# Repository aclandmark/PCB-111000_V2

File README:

PCB111000 has beeen developed as a learning aid for the C language when applied to AVR devices.  
It consists of a USB bridge to communicate with a PC, an 8 digit display and two AVR devices. 
One of the AVR devices (Atmega 328) hosts a programmer and miniOS which drives the display, 
the other (Atmega168), the user device, hosts user projects.

An I2C bus is used to link the two devices.
All user projects are compiled using Arduino, system projects use Arduino or Studio 7 if needed.
The boards are set up using the UNO to host a bespoke programer.  See repository "UNO_as_an_AVR_programer". 

See repository "PCB-111000/1_Documentation/1_PCB 111000 leaflet.pdf" for general information and a block diagram of the original development. 

There are three versions of PCB111000:

PCB_111000_V2 using two Atmega devices and the FTDI FT230XS USB bridge
PCB_111000_UNO_V2 A simplified plug in version for use with the UNO
PCB_111000_CP2102 Using one Atmega one ATtiny and a CP2102 module for USB connectivity.

In PCB_111000_UNO_V2 and PCB_111000_CP2102 the user device is an Atmega328 which hosts
a bootloader as well as the user projects.

In PCB_111000_CP2102 the I2C bus is replaced with a one wire firmware UART.

Originally 56 projects were developed for use with PCB111000.
These have been revised over the years and are now as follows

20 very short projects provided to show what a C program looks like and explore basic methods of program flow control
9 projects exploring the operation of the recever transmitter (USART) block
7 projects exploring interrupts
4 projects exploring bit operatons, division and the conversion between 8 bit binary and decimal numbers
11 projects based on the Arduino USART library with reset analysis including
	Interger, prime and scientific numbers
	Integer roots and a pie estimator
	Power series to compute real number powers and trig functions
	A floating point number to string sbroutine
	Displays to simulate gravity, the pendulum and a noise waveform.
9 Projects to Illustate driving the display from the keyboard and user switches, includes a simple
calculator and floating point number to 8 digit display.
7 Projects used to build simple clocks and stop watches
6 Projects used to illustrate use of Atmel Studio 7
8 projects used to illustrate the operation of floating point numbers, tested using power series as above
and the generation of pulse and sawtooth waveforms by supperimposing sine wave upon one another.
5 projects to test the operation of the PCB during assembly
5 projects used to exlore the calibration of the RC oscillators used to clock the devices.

Any bugs:	Of course there are especially in the conversion of a floating point number to 8 digits.
		Initially I tried to fix them, but stopped.  If they are of no interest to ayone else 
		then they are of no nterest to me either.

Projects for  PCB_111000_UNO_V2 and PCB_111000_CP2102:  Projects and the mini-OS for each of these pcbs 
requires updating however both include most of the initial projects.

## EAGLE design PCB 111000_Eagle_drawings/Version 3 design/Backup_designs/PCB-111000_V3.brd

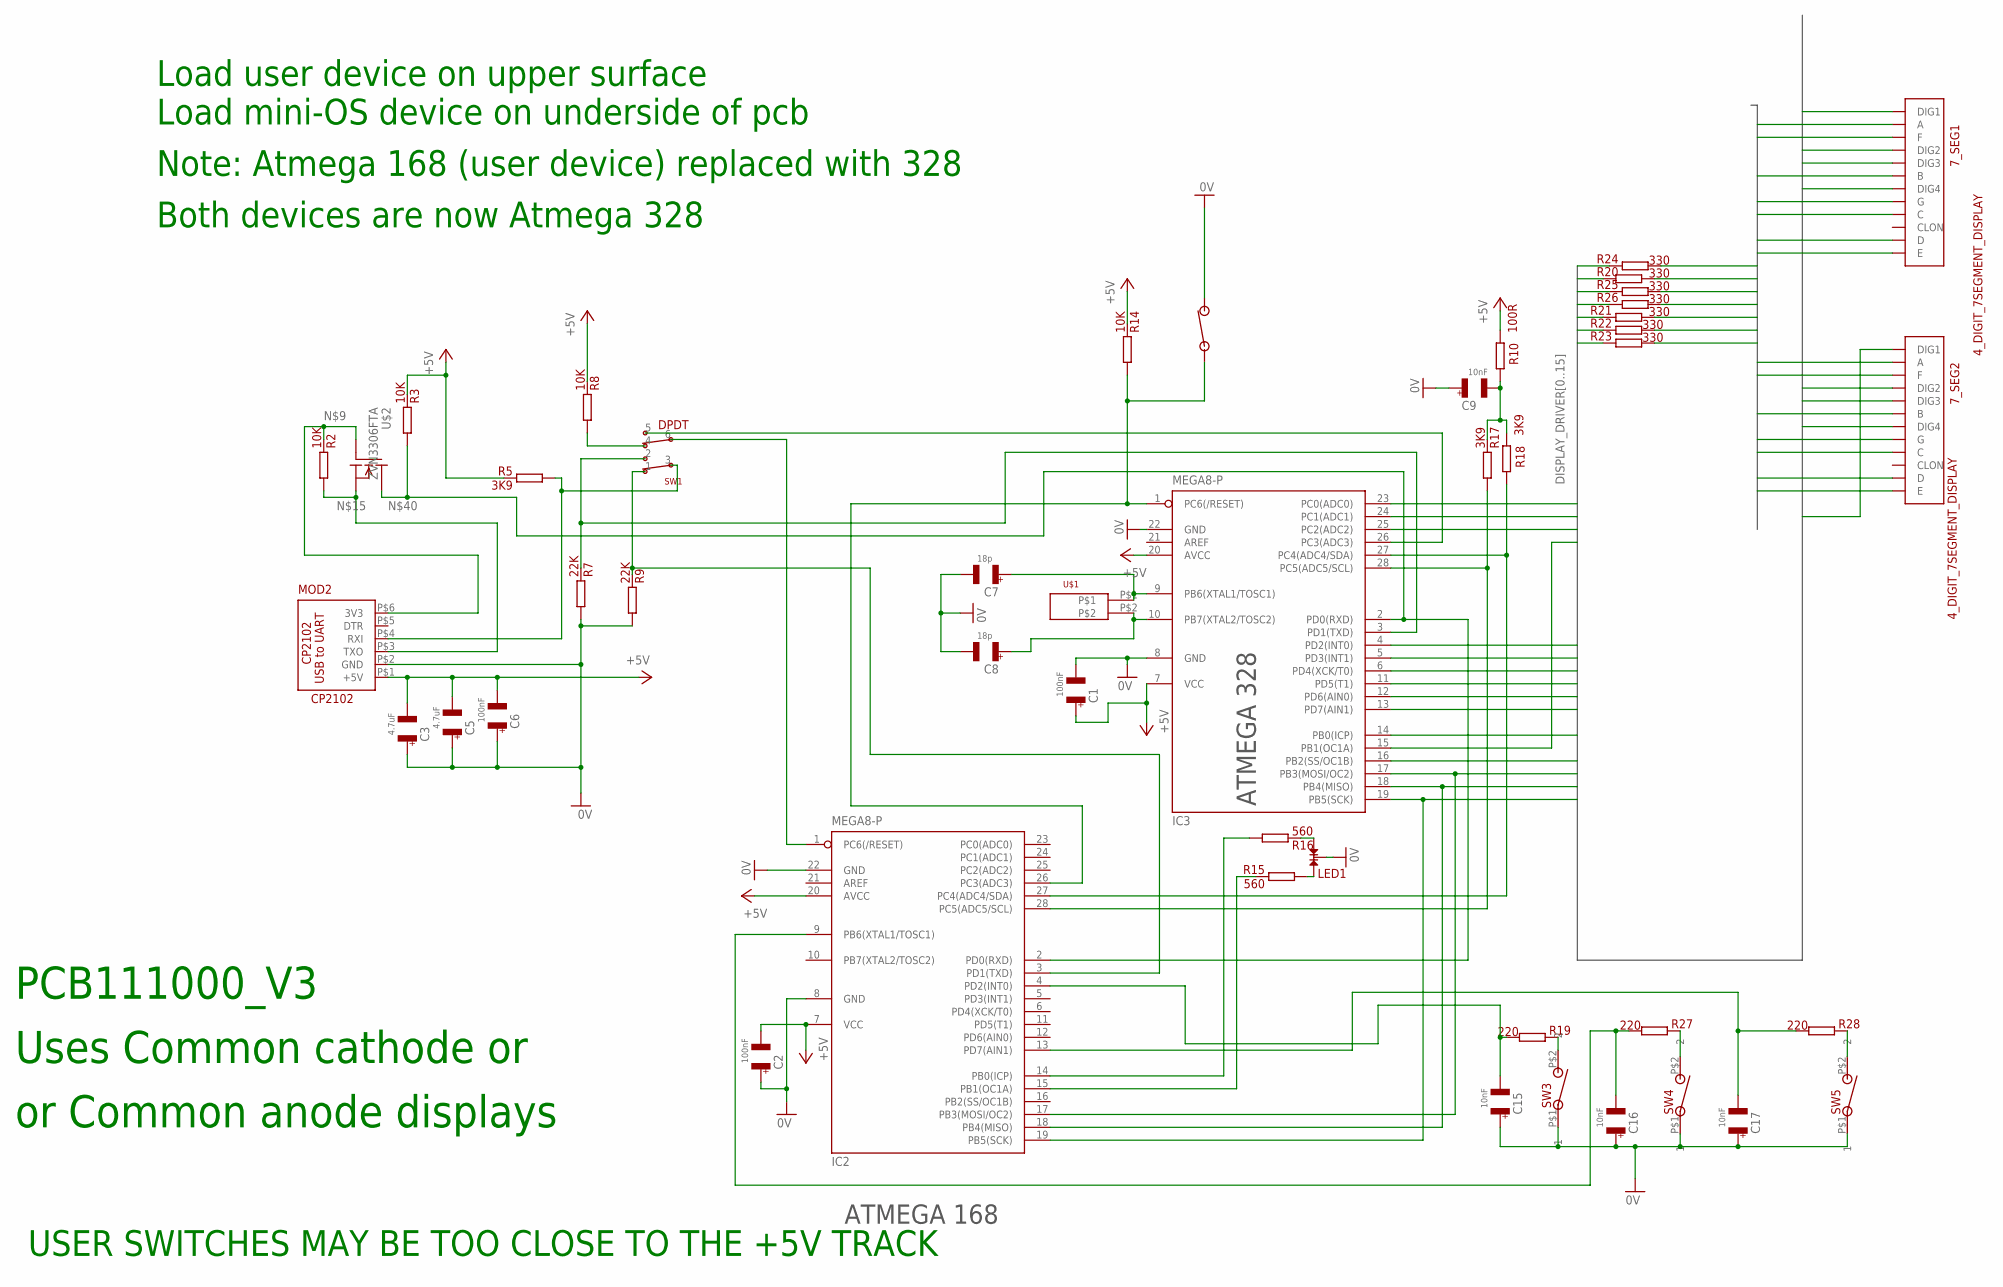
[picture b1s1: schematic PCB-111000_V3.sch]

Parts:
7_SEG1, 7_SEG2: 4_DIGIT_7SEGMENT_DISPLAY
C1, C2, C6: 100nF; 1206@1
C3, C5: 4.7uF; 1206@1
C7, C8: 18p; 0805
C9, C15, C16, C17: 10nF; 1206@1
IC2, IC3: MEGA8-P; DIL28-3
LED1: LED; CA_DUAL_LED
MOD2: CP2102
R2, R3, R8, R14: 10K; 1206
R5, R17, R18: 3K9; 1206
R7, R9: 22K; 1206
R10: 100R; 1206
R15, R16: 560; 1206
R19, R27, R28: 220; 1206
R20, R21, R22, R23, R24, R25, R26: 330; 1206
SW1: DPDT; DPDT_SWITCH
SW2: NO_SW; SM_NO_PUSH_BUTTON
SW3, SW4, SW5: NO_PB_1; RE51-0711
U$1: XTAL; XTAL_VIAS
U$2: ZVN3306FTA; SOT-23

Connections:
0V: C1.P$2 (2), C2.P$1 (1), C3.P$1 (1), C5.P$1 (1), C6.P$1 (1), C7.2, C8.2, C9.P$1 (1), C15.P$1 (1), C16.P$1 (1), C17.P$1 (1), IC2.8 (GND), IC2.22 (GND), IC3.8 (GND), IC3.22 (GND), LED1.2, MOD2.P$2 (GND), R7.P$1, R9.P$1, SW2.P$2 (2), SW3.P$1 (1), SW4.P$1 (1), SW5.P$1 (1)
+5V: C1.P$1 (1), C2.P$2 (2), C3.P$2 (2), C5.P$2 (2), C6.P$2 (2), IC2.7 (VCC), IC2.20 (AVCC), IC3.7 (VCC), IC3.20 (AVCC), MOD2.P$1 (+5V), R3.P$2, R5.P$2, R8.P$2, R10.P$2, R14.P$2
DISPLAY_DRIVER0: IC3.15 (PB1(OC1A)), R24.P$2
DISPLAY_DRIVER1: IC3.4 (PD2(INT0)), R20.P$2
DISPLAY_DRIVER2: IC3.5 (PD3(INT1)), R25.P$2
DISPLAY_DRIVER3: IC3.6 (PD4(XCK/T0)), R26.P$2
DISPLAY_DRIVER4: IC3.11 (PD5(T1)), R21.P$2
DISPLAY_DRIVER5: IC3.12 (PD6(AIN0)), R22.P$2
DISPLAY_DRIVER6: IC3.13 (PD7(AIN1)), R23.P$2
DISPLAY_DRIVER8: 7_SEG2.P$12 (DIG1), IC3.14 (PB0(ICP))
DISPLAY_DRIVER9: 7_SEG2.P$9 (DIG2), IC3.16 (PB2(SS/OC1B))
DISPLAY_DRIVER10: 7_SEG2.P$8 (DIG3), IC2.17 (PB3(MOSI/OC2)), IC3.17 (PB3(MOSI/OC2))
DISPLAY_DRIVER11: 7_SEG2.P$6 (DIG4), IC2.18 (PB4(MISO)), IC3.18 (PB4(MISO))
DISPLAY_DRIVER12: 7_SEG1.P$12 (DIG1), IC2.19 (PB5(SCK)), IC3.19 (PB5(SCK))
DISPLAY_DRIVER13: 7_SEG1.P$9 (DIG2), IC3.23 (PC0(ADC0))
DISPLAY_DRIVER14: 7_SEG1.P$8 (DIG3), IC3.24 (PC1(ADC1))
DISPLAY_DRIVER15: 7_SEG1.P$6 (DIG4), IC3.25 (PC2(ADC2))
unnamed: IC2.14 (PB0(ICP)), R16.P$1
unnamed: IC2.15 (PB1(OC1A)), R15.P$2
unnamed: LED1.1, R15.P$1
unnamed: LED1.3, R16.P$2
unnamed: IC3.26 (PC3(ADC3)), SW1.5
unnamed: IC3.3 (PD1(TXD)), R7.P$2, SW1.2
unnamed: R27.P$2, SW4.P$2 (2)
unnamed: R19.P$2, SW3.P$2 (2)
unnamed: MOD2.P$6 (3V3), R2.P$2, U$2.3 (G)
unnamed: C7.1, IC3.9 (PB6(XTAL1/TOSC1)), U$1.P$1
unnamed: C17.P$2 (2), IC2.13 (PD7(AIN1)), R28.P$1
unnamed: C8.1, IC3.10 (PB7(XTAL2/TOSC2)), U$1.P$2
unnamed: R8.P$1, SW1.4
unnamed: IC2.3 (PD1(TXD)), R9.P$2, SW1.1
unnamed: MOD2.P$3 (TXO), R2.P$1, U$2.2 (S)
unnamed: R28.P$2, SW5.P$2 (2)
unnamed: C15.P$2 (2), IC2.4 (PD2(INT0)), R19.P$1
unnamed: C16.P$2 (2), IC2.9 (PB6(XTAL1/TOSC1)), R27.P$1
unnamed: C9.P$2 (2), R10.P$1, R17.P$2, R18.P$2
unnamed: IC2.1 (PC6(/RESET)), SW1.6
unnamed: IC2.26 (PC3(ADC3)), IC3.1 (PC6(/RESET)), R14.P$1, SW2.P$1 (1)
unnamed: MOD2.P$4 (RXI), R5.P$1, SW1.3
unnamed: IC2.28 (PC5(ADC5/SCL)), IC3.28 (PC5(ADC5/SCL)), R17.P$1
unnamed: IC2.27 (PC4(ADC4/SDA)), IC3.27 (PC4(ADC4/SDA)), R18.P$1
unnamed: IC2.2 (PD0(RXD)), IC3.2 (PD0(RXD)), R3.P$1, U$2.1 (D)
SEVEN_SEG0: 7_SEG1.P$11 (A), 7_SEG2.P$11 (A), R24.P$1
SEVEN_SEG1: 7_SEG1.P$7 (B), 7_SEG2.P$7 (B), R20.P$1
SEVEN_SEG2: 7_SEG1.P$4 (C), 7_SEG2.P$4 (C), R25.P$1
SEVEN_SEG3: 7_SEG1.P$2 (D), 7_SEG2.P$2 (D), R26.P$1
SEVEN_SEG4: 7_SEG1.P$1 (E), 7_SEG2.P$1 (E), R21.P$1
SEVEN_SEG5: 7_SEG1.P$10 (F), 7_SEG2.P$10 (F), R22.P$1
SEVEN_SEG6: 7_SEG1.P$5 (G), 7_SEG2.P$5 (G), R23.P$1

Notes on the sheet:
ATMEGA 168
ATMEGA 328
or Common anode displays
PCB111000_V3
Uses Common cathode or
USER SWITCHES MAY BE TOO CLOSE TO THE +5V TRACK
Load mini-OS device on underside of pcb
Load user device on upper surface
Note: Atmega 168 (user device) replaced with 328
Both devices are now Atmega 328

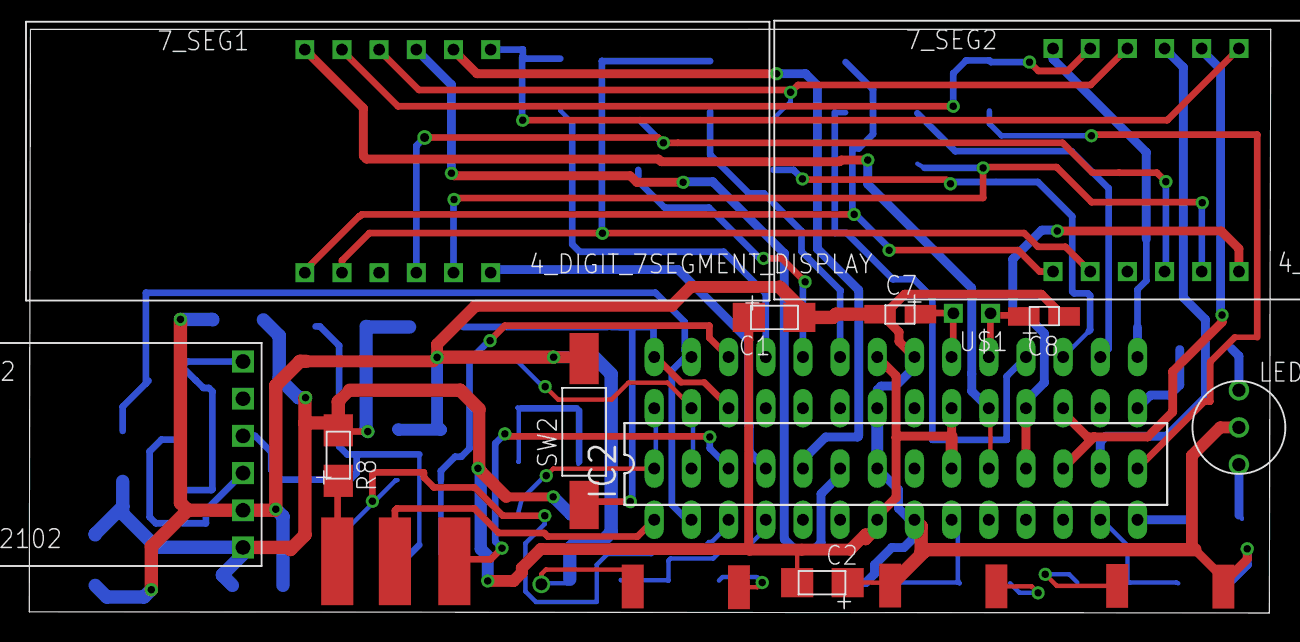
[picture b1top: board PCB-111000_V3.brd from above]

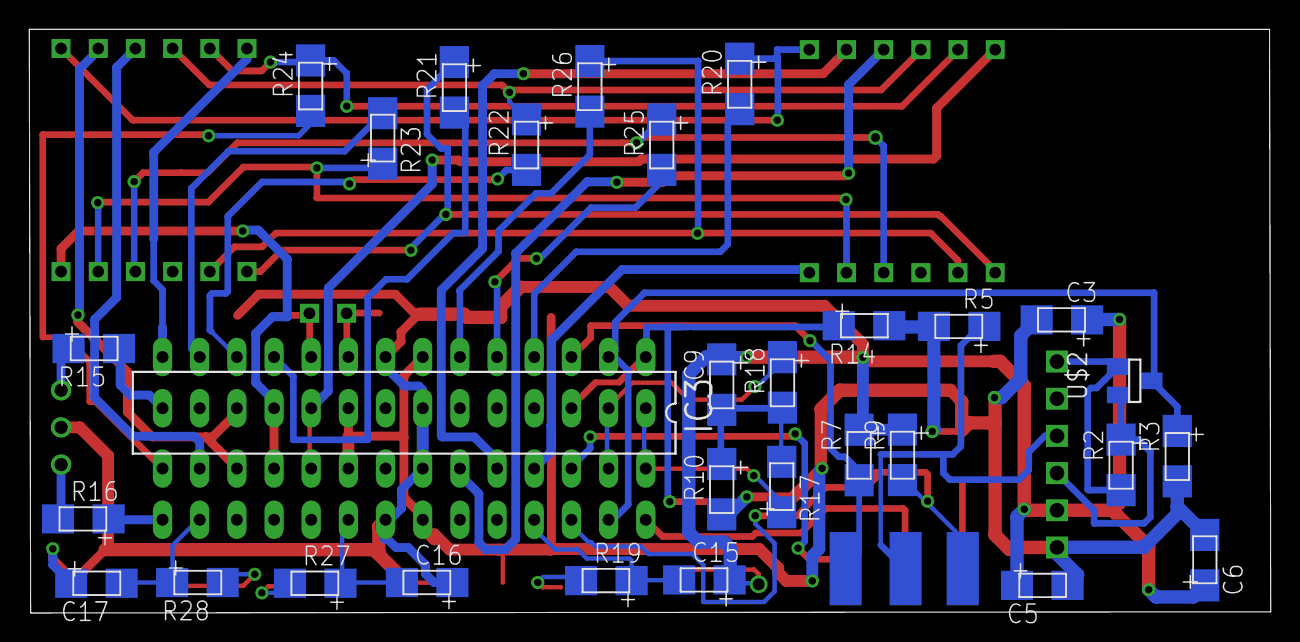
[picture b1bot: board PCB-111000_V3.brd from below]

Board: 2 copper layers, 84.8 x 39.9 mm, 46 parts (31 on the bottom side), 49 nets.

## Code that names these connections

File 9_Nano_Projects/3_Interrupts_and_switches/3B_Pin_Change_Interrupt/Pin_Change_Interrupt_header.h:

#include <avr/wdt.h>

char watch_dog_reset = 0;

#define T0_delay_10ms 5,178
#define T1_delay_100ms 3, 0x9E62
#define T2_delay_10ms 7,178


#define set_up_PCI_on_sw2           PCICR |= (1 << PCIE0);
#define enable_pci_on_sw2           PCMSK0 |= (1 << PCINT6);


#define switch_3_down  ((PIND & 0x80)^0x80)
#define switch_3_up   (PIND & 0x80)
#define switch_1_down ((PIND & 0x04)^0x04)
#define switch_1_up   (PIND & 0x04)
#define switch_2_down ((PINB & 0x40)^0x40)
#define switch_2_up   (PINB & 0x40)

/*****************************************************************************/
#define setup_HW \
setup_watchdog;\
set_up_I2C;\
ADMUX |= (1 << REFS0);\
set_up_switched_inputs;\
Set_LED_ports;\
Unused_I_O;\
eeprom_write_byte((uint8_t*)(0x1FD),OSCCAL);\
while (!(PIND & (1 << PD1)));\
Timer_T0_10mS_delay_x_m(5);\
OSC_CAL;\
setup_PC_comms_Basic(0,16);\
I2C_Tx_LED_dimmer();\
\
\
/*OPTIONAL Setup_HW code gives default ap*/\
Timer_T0_10mS_delay_x_m(1);\
I2C_TX_328_check();\
waiting_for_I2C_master;\
if (receive_byte_with_Nack()==1)\
{TWCR = (1 << TWINT);\
wdt_enable(WDTO_30MS);\
I2C_Tx_display();}\
else TWCR = (1 << TWINT);



/*****************************************************************************/
#define setup_watchdog \
if (MCUSR & (1 << WDRF))watch_dog_reset = 1;\
wdr();\
MCUSR &= ~(1<<WDRF);\
WDTCSR |= (1 <<WDCE) | (1<< WDE);\
WDTCSR = 0;

#define wdr()  __asm__ __volatile__("wdr")

#define SW_reset {wdt_enable(WDTO_30MS);while(1);}



/*****************************************************************************/
#define set_up_I2C \
TWAR = 0x02;



/*****************************************************************************/
#define set_up_switched_inputs \
MCUCR &= (~(1 << PUD));\
DDRD &= (~((1 << PD2)|(1 << PD7)));\
PORTD |= ((1 << PD2) | (1 << PD7));\
DDRB &= (~(1 << PB6));\
PORTB |= (1 << PB6);



/*****************************************************************************/
#define Unused_I_O \
MCUCR &= (~(1 << PUD));\
DDRB &= (~((1 << PB2)|(1 << PB7)));\
DDRC &= (~((1 << PC0)|(1 << PC1)|(1 << PC2)));\
DDRD &= (~((1 << PD3)|(1 << PD4)|(1 << PD5)|(1 << PD6)));\
PORTB |= ((1 << PB2)|(1 << PB7));\
PORTC |= ((1 << PC0)|(1 << PC1)|(1 << PC2));\
PORTD |= ((1 << PD3)|(1 << PD4)|(1 << PD5)|(1 << PD6));



/*****************************************************************************/
#define Set_LED_ports   DDRB = (1 << DDB0) | (1 << DDB1);
#define LEDs_on       PORTB |= (1 << PB0)|(1 << PB1);
#define LEDs_off      PORTB &= (~((1 << PB0)|(1 << PB1)));
#define LED_1_on      PORTB |= (1 << PB1);
#define LED_1_off     PORTB &= (~( 1<< PB1)); 
#define LED_2_off     PORTB &= (~(1 << PB0));
#define LED_2_on      PORTB |= (1 << PB0);

#define Toggle_LED_1 \
if (PORTB & (1 << PB1)){LED_1_off;}\
else {PORTB |= (1 << PB1);}



/*****************************************************************************/
#define OSC_CAL \
if ((eeprom_read_byte((uint8_t*)0x1FE) > 0x0F)\
&&  (eeprom_read_byte((uint8_t*)0x1FE) < 0xF0) && (eeprom_read_byte((uint8_t*)0x1FE)\
== eeprom_read_byte((uint8_t*)0x1FF))) {OSCCAL = eeprom_read_byte((uint8_t*)0x1FE);}



/*****************************************************************************/
#define diagnostic_mode \




/*****************************************************************************/
#define waiting_for_I2C_master \
TWCR = (1 << TWEA) | (1 << TWEN);\
while (!(TWCR & (1 << TWINT)));\
TWDR;

#define clear_I2C_interrupt \
TWCR = (1 << TWINT);



/*****************************************************************************/
#include "Resources_nano_projects/Subroutines/HW_timers.c"
#include "Resources_nano_projects/PC_comms/Basic_Rx_Tx_Basic.c"
#include "Resources_nano_projects/Chip2chip_comms/I2C_subroutines_1.c"
//#include "Resources_nano_projects/I2C_Subroutines/I2C_subroutines_2.c"
#include "Resources_nano_projects/Chip2chip_comms/I2C_slave_Rx_Tx.c"
//#include "Resources_nano_projects/I2C_Subroutines/I2C_diagnostic.c"
#include "Resources_nano_projects/Subroutines/Random_and_prime_nos.c"




/******************************************************************************/

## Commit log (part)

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2025-11-21 Create PCB-111000_V3_Fusion_parts_list
2025-11-22 Update PCB-111000_V3_Fusion_parts_list
